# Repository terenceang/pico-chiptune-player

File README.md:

# Pico Chiptune Player

**Version:** 0.8 (JLC Assembly Prep — corrected GPIO map, 0402/0805 passives, LCSC part numbers)  
**Author:** Terence Ang <terenceang@mac.com>  
**Company:** MotionFxDesign  
**License:** [CC BY-NC-SA 4.0](LICENSE) (Creative Commons Attribution-NonCommercial-ShareAlike 4.0 International) — **NOT FOR COMMERCIAL USE**  

---

## Overview

The **Pico Chiptune Player** is an open-hardware music player powered by an on-board **Raspberry Pi RP2354A** microcontroller (QFN-60 with 2 MB internal stacked QSPI NOR flash) driving two authentic **Yamaha YM2149F** Programmable Sound Generators (PSGs), register-compatible with the General Instrument AY-3-8910. Each PSG provides 3 voices, giving **6 independent voices** total, routed through a **software-controlled 4-mode analog stereo/mono mixing matrix** (`2× 74HCT4053D`).

It enables standalone playback of classic AY-3-8910 / YM2149 chiptune music formats (e.g., `.ym`, `.vgm`, `.psg`, `.pt3`, `.sndh`) loaded directly from an onboard microSD card, with song and playback metadata displayed on an I2C OLED display.

---

## Hardware Highlights (Rev 0.8)

- **Microcontroller (`U5`):** Bare **Raspberry Pi RP2354A** (QFN-60, 7×7 mm, 0.4 mm pitch) with **2 MB internal stacked QSPI NOR flash** and all **30 Bank-0 GPIOs (`GPIO0..GPIO29`)** exposed, clocked by a 12 MHz SMD-3225 crystal (`Y1`, `C20`/`C21` = 15 pF, `R16` = 1 kΩ) with internal 1.1 V core buck regulator (`L1` = 3.3 µH) and onboard `BOOTSEL` (`SW4`) and `RESET` (`SW5`) SMD tactile buttons (`TS-1187A`, LCSC `C318884`).
- **USB-C 5V/3A Power & 3-Stage Sequencing (`J1`, `D1`, `U6`, `Q1`, `Q2`):**
  - 16-pin USB 2.0 Type-C receptacle (`J1`) with independent 5.1 kΩ 1% pull-downs (`R21`, `R22`) on `CC1`/`CC2` advertising a fixed 5V/3A sink, plus `USBLC6-2SC6` (`D1`) ESD protection and 27 Ω (`R17`, `R18`) USB series termination.
  - **Stage 1 (`VBUS` → `+3.3V` & `+1V1`):** `AMS1117-3.3` (`U6`) powers `+3.3V` (`RP2354A` `IOVDD`, microSD `J2`, OLED `U2`) and the `RP2354A` internal `+1V1` core regulator immediately on USB plug-in so `RP2354A` I/O pins initialize cleanly with `~RESET` held LOW (`R3` = 10 kΩ).
  - **Stage 2 (`+3.3V` RC-delayed → `+5V`):** RC delay (`R23` = 47 kΩ, `C31` = 100 nF) turns on N-MOSFET `Q2` (`2N7002`), pulling down the gate of high-side P-MOSFET `Q1` (`AO3401A`, with `R28` = 100 kΩ pull-up and `C32` = 10 nF soft-start cap) to switch `VBUS` onto the `+5V` rail **only after `+3.3V` is stable**, preventing unpowered latch-up or back-bias on the 5 V `YM2149F` PSGs (`U1`, `U4`), `74HCT4053D` analog switches (`U8`, `U9`), and `PAM8403` amplifier (`U3`).
  - **Stage 3 (`SD_Amp` on `GPIO21` → `U3` `PAM8403`):** `R13` (10 kΩ pull-down) keeps `PAM8403` `~MUTE` and `~SHDN` LOW during Stage 1 & Stage 2 power-up until firmware drives `GPIO21` HIGH after AC coupling capacitors `C3`/`C10` settle, eliminating power-on pop.
- **Sound Generators (`U1`, `U4`):** 2× Yamaha YM2149F (40-pin DIP, socketed), 6 voices total; a matched pair of AY-3-8910s also fits with `JP1` open.
- **4-Mode Hardware Stereo/Mono Analog Mixing Matrix (`U8`, `U9`):**
  - Dual `74HCT4053D` triple 2:1 analog multiplexers powered from `+5V` (`VCC = +5V`, `VEE = VSS = INH = GND`, 3.3 V TTL-compatible control inputs) controlled by `GPIO14` (`MUX_PAN`), `GPIO15` (`MUX_B_CEN`), `GPIO16` (`MUX_C_CEN`), and `GPIO17` (`MUX_MONO`) with 470 Ω (`R14`, `R15`) `-3 dB` center-channel compensation resistors.
  - Supports **Dual-PSG Split Stereo** (`U1`=Left, `U4`=Right), **ABC Stereo** (`A`=Left, `B`=Center, `C`=Right across both PSGs), **ACB Stereo** (`A`=Left, `C`=Center, `B`=Right across both PSGs), and **True Mono** (`A+B+C` of both PSGs summed equally to Left & Right).
- **Audio Amplifier & Output (`U3`, `J3`, `J4`):**
  - Two passive summing/filtering networks (`R4`,`R5`,`R7`,`R8`,`C4`,`C3` for Left; `R9`,`R10`,`R11`,`R12`,`C9`,`C10` for Right) feeding an on-board **PAM8403 3W+3W filterless Class-D stereo amplifier** (`U3`, SOIC-16).
  - JST-PH 2-pin speaker connectors `J3` (left) / `J4` (right) with bridge-tied outputs for 4–8 Ω speakers.
- **Storage (`J2`):** 4-bit SDIO microSD card socket (Hirose `DM3AT-SF-PEJM5`, LCSC `C114218`) driven by the RP2350 PIO-based `pico_sd_card` driver; card presence detected in software (`R1` 10 kΩ pull-up on `DAT3`).
- **Display (`U2`) & Controls (`SW1..SW5`):** 0.96" SSD1306 128×64 I2C OLED display (`U2`), 3 navigation pushbuttons (`SW1` Play/Pause, `SW2` Next, `SW3` Prev), plus `SW4` (`BOOTSEL`) and `SW5` (`RESET`) — all `TS-1187A` SMD tactiles (LCSC `C318884`).
- **Clock Divider Select (`JP1`):** Solder jumper for the YM2149F ÷2 internal clock divider (`/SEL`, pin 26), shared by both PSGs.

---

## Pinout Summary (`U5` — RP2354A QFN-60)

| GPIO | QFN-60 Pin | Net / Signal | Connected Subsystem |
| :--- | :---: | :--- | :--- |
| **`GPIO0..GPIO3`** | Pins 2..5 | `DA0..DA3` | YM2149F 8-Bit Data Bus Bits 0..3, shared by `U1`/`U4` (Pins 37..34) |
| **`GPIO4..GPIO7`** | Pins 7..10 | `DA4..DA7` | YM2149F 8-Bit Data Bus Bits 4..7, shared by `U1`/`U4` (Pins 33..30) |
| **`GPIO8`** | Pin 12 | `BC1` | PSG1 (`U1`) Bus Control 1 (Pin 29) |
| **`GPIO9`** | Pin 13 | `MCU_CLK` | YM2149F Master Clock Input, shared by `U1`/`U4` (Pin 22 via 33 Ω series `R2`) |
| **`GPIO10`** | Pin 14 | `BDIR` | PSG1 (`U1`) Bus Direction Control (Pin 27) |
| **`GPIO11`** | Pin 15 | `~RESET` | YM2149F Active-Low Reset, shared by `U1`/`U4` (Pin 23) + 10 kΩ `R3` pull-down |
| **`GPIO12`** | Pin 16 | `BC1_2` | PSG2 (`U4`) Bus Control 1 (Pin 29) |
| **`GPIO13`** | Pin 17 | `BDIR2` | PSG2 (`U4`) Bus Direction Control (Pin 27) |
| **`GPIO14`** | Pin 18 | `MUX_PAN` | Stereo Matrix Right/Left Voice Pan (`U9` Pins 9, 10, 11 + 10 kΩ `R24` pull-down) |
| **`GPIO15`** | Pin 19 | `MUX_B_CEN` | Stereo Matrix Voice B Center Enable (`U8` Pin 11 + 10 kΩ `R25` pull-down) |
| **`GPIO16`** | Pin 27 | `MUX_C_CEN` | Stereo Matrix Voice C Center Enable (`U8` Pin 10 + 10 kΩ `R26` pull-down) |
| **`GPIO17`** | Pin 28 | `MUX_MONO` | Stereo Matrix True Mono Bridge Enable (`U8` Pin 9 + 10 kΩ `R27` pull-down) |
| **`GPIO18`** | Pin 29 | `SW_NEXT` | Next Track Button (`SW2`) |
| **`GPIO19`** | Pin 31 | `SW_PLAY` | Play / Pause Button (`SW1`) |
| **`GPIO20`** | Pin 32 | `SW_PREV` | Previous Track Button (`SW3`) |
| **`GPIO21`** | Pin 33 | `SD_Amp` | PAM8403 Audio Amp Enable / Mute (`U3` Pins 5 `~MUTE` & 12 `~SHDN`, `R13` pull-down) |
| **`GPIO22`** | Pin 34 | `SD_DAT0` | MicroSD SDIO Data 0 (`J2` Pin 7) |
| **`GPIO23`** | Pin 35 | `SD_DAT1` | MicroSD SDIO Data 1 (`J2` Pin 8) |
| **`GPIO24`** | Pin 36 | `SD_DAT2` | MicroSD SDIO Data 2 (`J2` Pin 1) |
| **`GPIO25`** | Pin 37 | `SD_DAT3` | MicroSD SDIO Data 3 (`J2` Pin 2 + 10 kΩ `R1` pull-up) |
| **`GPIO26`** | Pin 40 | `SD_CLK` | MicroSD SDIO Clock (`J2` Pin 5) |
| **`GPIO27`** | Pin 41 | `SD_CMD` | MicroSD SDIO Command (`J2` Pin 3) |
| **`GPIO28`** | Pin 42 | `OLED_SDA` | 0.96" OLED I2C0 SDA (`U2` Pin 4) |
| **`GPIO29`** | Pin 43 | `OLED_SCL` | 0.96" OLED I2C0 SCL (`U2` Pin 3) |

---

## 4-Mode Stereo / Mono Mixing Matrix Truth Table

| Mode | `MUX_MONO` (`GPIO17`) | `MUX_B_CEN` (`GPIO15`) | `MUX_C_CEN` (`GPIO16`) | `MUX_PAN` (`GPIO14`) | Left Channel (`AMP_INL`) | Right Channel (`AMP_INR`) | Use Case |
| :--- | :---: | :---: | :---: | :---: | :--- | :--- | :--- |
| **0: Dual-PSG Split (Default)** | `0` | `0` | `0` | `0` | `U1` (`A1 + B1 + C1`) | `U4` (`A2 + B2 + C2`) | 6-voice TurboSound / Dual-PSG tracks (chip 1 Left, chip 2 Right); default at boot via `R24..R27` pull-downs |
| **1: ABC Stereo** | `0` | `1` | `0` | `1` | `A1 + A2` + `0.71×(B1 + B2)` | `C1 + C2` + `0.71×(B1 + B2)` | Standard Western / Atari ST / ZX Spectrum ABC stereo (`A`=Left, `B`=Center `-3 dB`, `C`=Right) |
| **2: ACB Stereo** | `0` | `0` | `1` | `0` | `A1 + A2` + `0.71×(C1 + C2)` | `B1 + B2` + `0.71×(C1 + C2)` | Eastern European / Pentagon / PT3 ACB stereo (`A`=Left, `C`=Center `-3 dB`, `B`=Right) |
| **3: True Mono** | `1` | `0` | `0` | `0` | `0.5×(U1 + U4)` (`A+B+C`) | `0.5×(U1 + U4)` (`A+B+C`) | Classic single-PSG mono chiptunes played identically through both speakers |

**Rev 0.8** is prepared for JLC PCB assembly: every part carries an `LCSC Part #` in the schematic, passives are JLC basic 0402/0805 parts, and the microSD socket (`C114218`) and buttons (`C318884`) are SMD.

For the complete hardware design details, circuit topology, and full Bill of Materials with LCSC part numbers, refer to [HARDWARE.md](HARDWARE.md).

---

## License & Commercial Use Notice

Copyright (c) 2026 Terence Ang <terenceang@mac.com> / MotionFxDesign.

This project is licensed under the **Creative Commons Attribution-NonCommercial-ShareAlike 4.0 International License (CC BY-NC-SA 4.0)**.

> **NOT FOR COMMERCIAL USE**  
> This design, including schematics, PCB layouts, Gerber files, firmware, and documentation, is free for personal, hobby, educational, and non-commercial use.  
> **Commercial manufacture, distribution, sale, or bundling for profit is strictly prohibited** without prior written authorization from Terence Ang (<terenceang@mac.com>).

See the [LICENSE](LICENSE) file for the complete license terms.

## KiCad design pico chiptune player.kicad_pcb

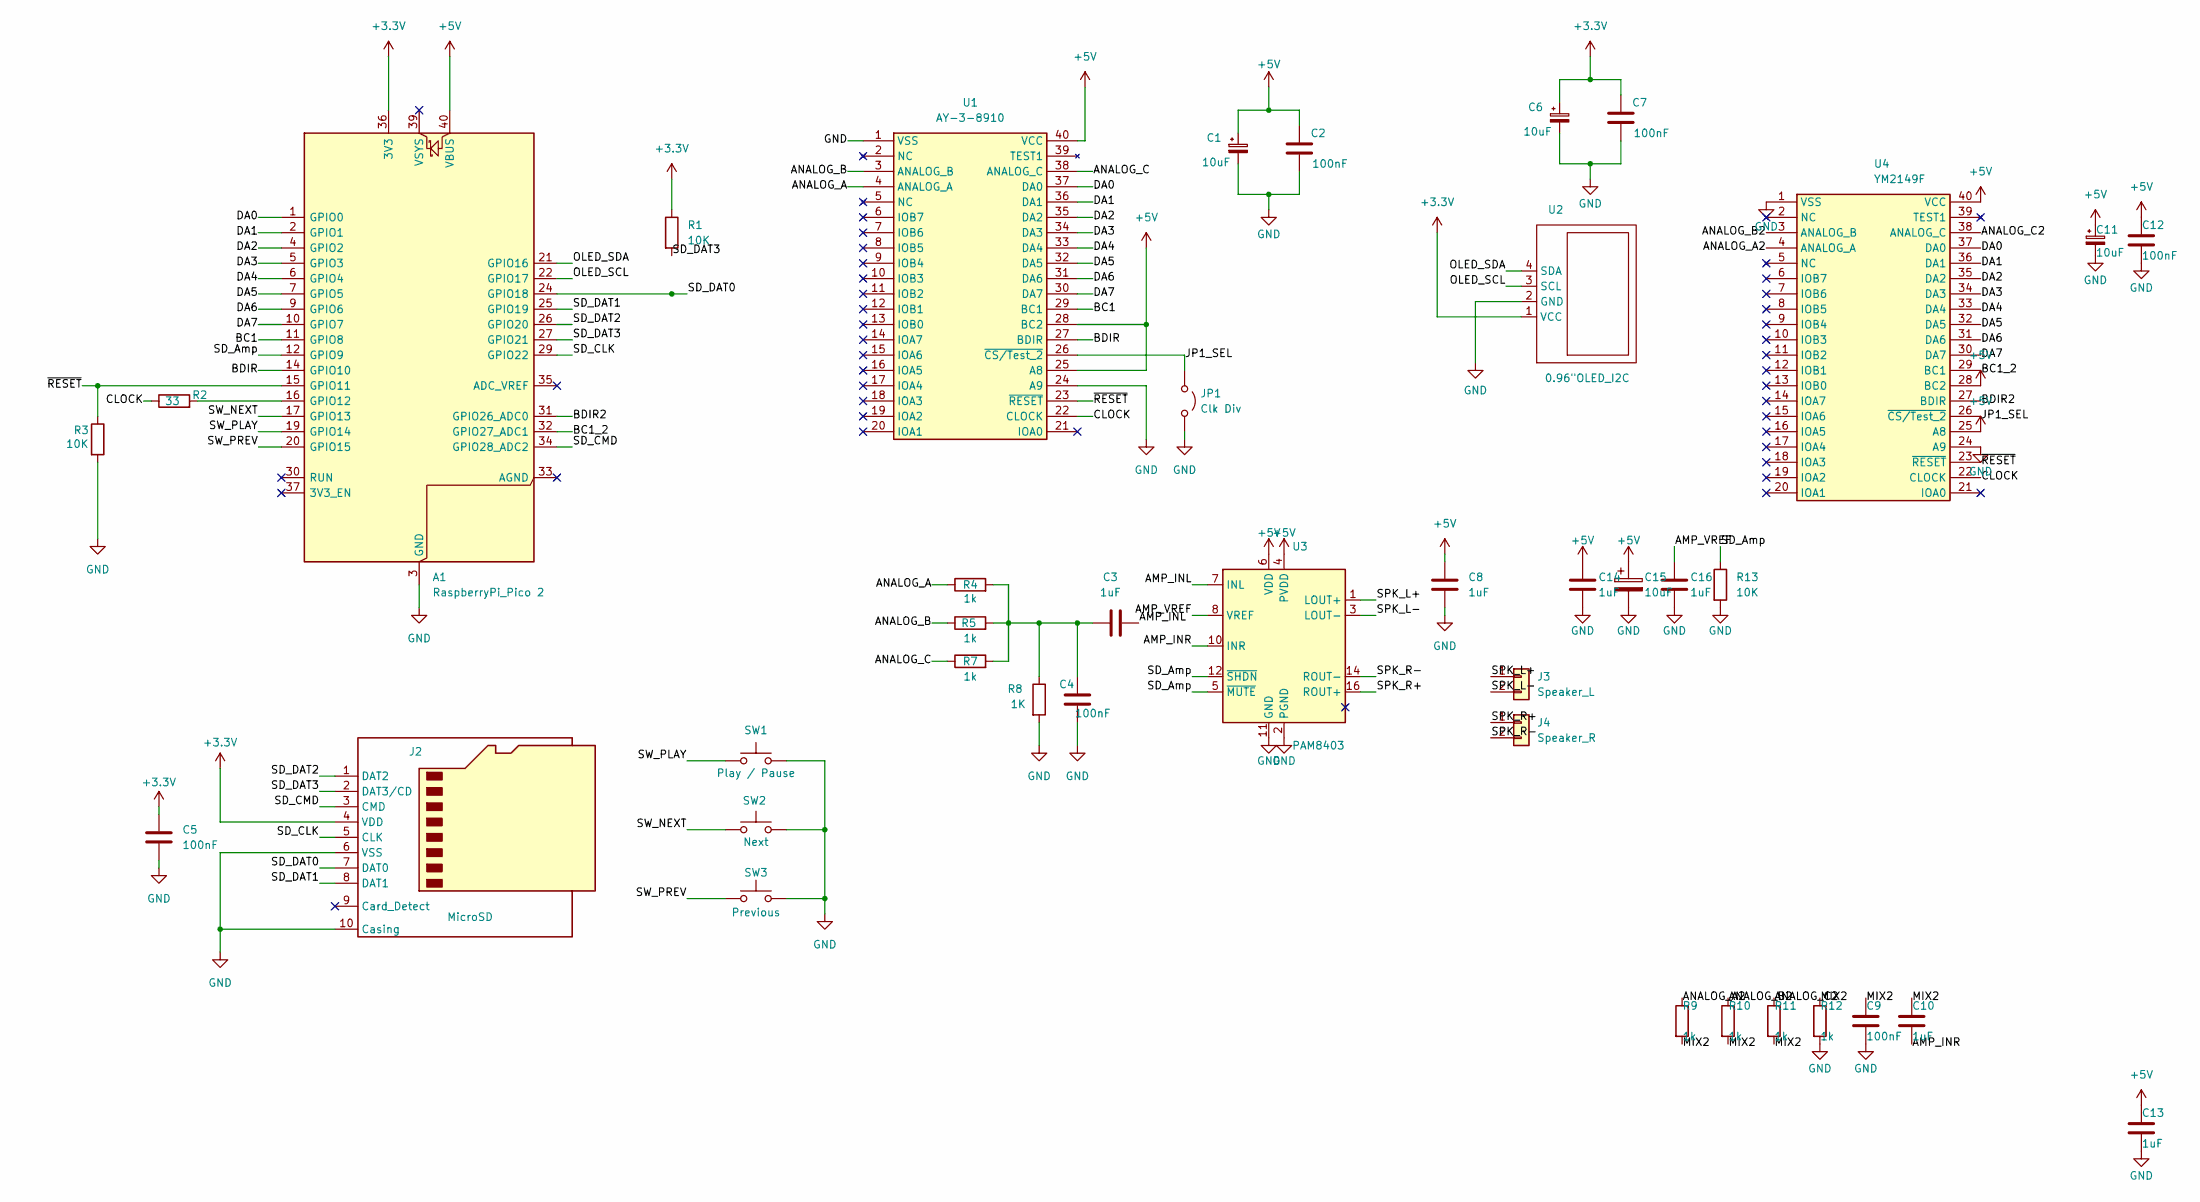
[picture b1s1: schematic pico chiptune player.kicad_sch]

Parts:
A1: RaspberryPi_Pico 2; RPi_Pico_SMD_TH
C1, C6, C15: 10uF; CP_Elec_4x5.4; LCSC Part # C3343
C2, C7: 100nF; C_0805_2012Metric_Pad1.18x1.45mm_HandSolder; LCSC Part # C1711
C3, C8, C10, C13, C14, C16: 1uF; C_0805_2012Metric_Pad1.18x1.45mm_HandSolder; LCSC Part # C28323
C4, C5: 100nF; C_0805_2012Metric_Pad1.18x1.45mm_HandSolder; LCSC Part # C1710
C9, C12: 100nF; C_0805_2012Metric_Pad1.18x1.45mm_HandSolder
C11: 10uF; CP_Elec_4x5.4
J2: MicroSD; LCSC Part # C479742
J3: Speaker_L; JST_PH_B2B-PH-K_1x02_P2.00mm_Vertical; LCSC Part # C131337
J4: Speaker_R; JST_PH_B2B-PH-K_1x02_P2.00mm_Vertical; LCSC Part # C131337
JP1: Clk Div; SolderJumper-2_P1.3mm_Open_TrianglePad1.0x1.5mm
R1, R3, R13: 10K; R_0805_2012Metric_Pad1.20x1.40mm_HandSolder; LCSC Part # C17414
R2: 33; R_0805_2012Metric_Pad1.20x1.40mm_HandSolder; LCSC Part # C17634
R4, R5, R7: 1k; R_0805_2012Metric_Pad1.20x1.40mm_HandSolder; LCSC Part # C17513
R8: 1K; R_0805_2012Metric_Pad1.20x1.40mm_HandSolder; LCSC Part # C17513
R9, R10, R11, R12: 1k; R_0805_2012Metric_Pad1.20x1.40mm_HandSolder
SW1: Play / Pause; SW_PUSH_6mm; LCSC Part # C17513
SW2: Next; SW_PUSH_6mm; LCSC Part # C114217
SW3: Previous; SW_PUSH_6mm; LCSC Part # C12740
U1: AY-3-8910; DIP-40_W15.24mm
U2: 0.96"OLED_I2C; OLED 0.96 I2C
U3: PAM8403; SOIC-16_3.9x9.9mm_P1.27mm; LCSC Part # C5122557
U4: YM2149F; DIP-40_W15.24mm

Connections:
+3.3V: A1.36 (3V3), C5.1, C6.1, C7.1, J2.4 (VDD), R1.1, U2.1 (VCC)
+5V: A1.40 (VBUS), C1.1, C2.1, C8.1, C11.1, C12.1, C13.1, C14.1, C15.1, U1.25 (A8), U1.28 (BC2), U1.40 (VCC), U3.4 (PVDD), U3.6 (VDD), U3.13 (PVDD), U4.25 (A8), U4.28 (BC2), U4.40 (VCC)
/AMP_INL: C3.2, U3.7 (INL)
/AMP_INR: C10.2, U3.10 (INR)
/AMP_VREF: C16.1, U3.8 (VREF)
/ANALOG_A: R4.1, U1.4 (ANALOG_A)
/ANALOG_A2: R9.1, U4.4 (ANALOG_A)
/ANALOG_B: R5.1, U1.3 (ANALOG_B)
/ANALOG_B2: R10.1, U4.3 (ANALOG_B)
/ANALOG_C: R7.1, U1.38 (ANALOG_C)
/ANALOG_C2: R11.1, U4.38 (ANALOG_C)
/BC1: A1.11 (GPIO8), U1.29 (BC1)
/BC1_2: A1.32 (GPIO27_ADC1), U4.29 (BC1)
/BDIR: A1.14 (GPIO10), U1.27 (BDIR)
/BDIR2: A1.31 (GPIO26_ADC0), U4.27 (BDIR)
/CLOCK: R2.1, U1.22 (CLOCK), U4.22 (CLOCK)
/DA0: A1.1 (GPIO0), U1.37 (DA0), U4.37 (DA0)
/DA1: A1.2 (GPIO1), U1.36 (DA1), U4.36 (DA1)
/DA2: A1.4 (GPIO2), U1.35 (DA2), U4.35 (DA2)
/DA3: A1.5 (GPIO3), U1.34 (DA3), U4.34 (DA3)
/DA4: A1.6 (GPIO4), U1.33 (DA4), U4.33 (DA4)
/DA5: A1.7 (GPIO5), U1.32 (DA5), U4.32 (DA5)
/DA6: A1.9 (GPIO6), U1.31 (DA6), U4.31 (DA6)
/DA7: A1.10 (GPIO7), U1.30 (DA7), U4.30 (DA7)
/JP1_SEL: JP1.1 (A), U1.26 (~CS/Test_2), U4.26 (~CS/Test_2)
/MIX2: C9.1, C10.1, R9.2, R10.2, R11.2, R12.1
/OLED_SCL: A1.22 (GPIO17), U2.3 (SCL)
/OLED_SDA: A1.21 (GPIO16), U2.4 (SDA)
/SD_Amp: A1.12 (GPIO9), R13.1, U3.5 (~MUTE), U3.12 (~SHDN)
/SD_CLK: A1.29 (GPIO22), J2.5 (CLK)
/SD_CMD: A1.34 (GPIO28_ADC2), J2.3 (CMD)
/SD_DAT0: A1.24 (GPIO18), J2.7 (DAT0)
/SD_DAT1: A1.25 (GPIO19), J2.8 (DAT1)
/SD_DAT2: A1.26 (GPIO20), J2.1 (DAT2)
/SD_DAT3: A1.27 (GPIO21), J2.2 (DAT3/CD), R1.2
/SPK_L+: J3.1, U3.1 (LOUT+)
/SPK_L-: J3.2, U3.3 (LOUT-)
/SPK_R+: J4.1, U3.16 (ROUT+)
/SPK_R-: J4.2, U3.14 (ROUT-)
/SW_NEXT: A1.17 (GPIO13), SW2.1
/SW_PLAY: A1.19 (GPIO14), SW1.1
/SW_PREV: A1.20 (GPIO15), SW3.1
/~RESET: A1.15 (GPIO11), R3.1, U1.23 (~RESET), U4.23 (~RESET)
GND: A1.3 (GND), A1.8 (GND), A1.13 (GND), A1.18 (GND), A1.23 (GND), A1.28 (GND), A1.38 (GND), C1.2, C2.2, C4.2, C5.2, C6.2, C7.2, C8.2, C9.2, C11.2, C12.2, C13.2, C14.2, C15.2, C16.2, J2.6 (VSS), J2.10 (Casing), JP1.2 (B), R3.2, R8.2, R12.2, R13.2, SW1.2, SW2.2, SW3.2, U1.1 (VSS), U1.24 (A9), U2.2 (GND), U3.2 (PGND), U3.11 (GND), U3.15 (PGND), U4.1 (VSS), U4.24 (A9)
unnamed: A1.16 (GPIO12), R2.2
unnamed: C3.1, C4.1, R4.2, R5.2, R7.2, R8.1

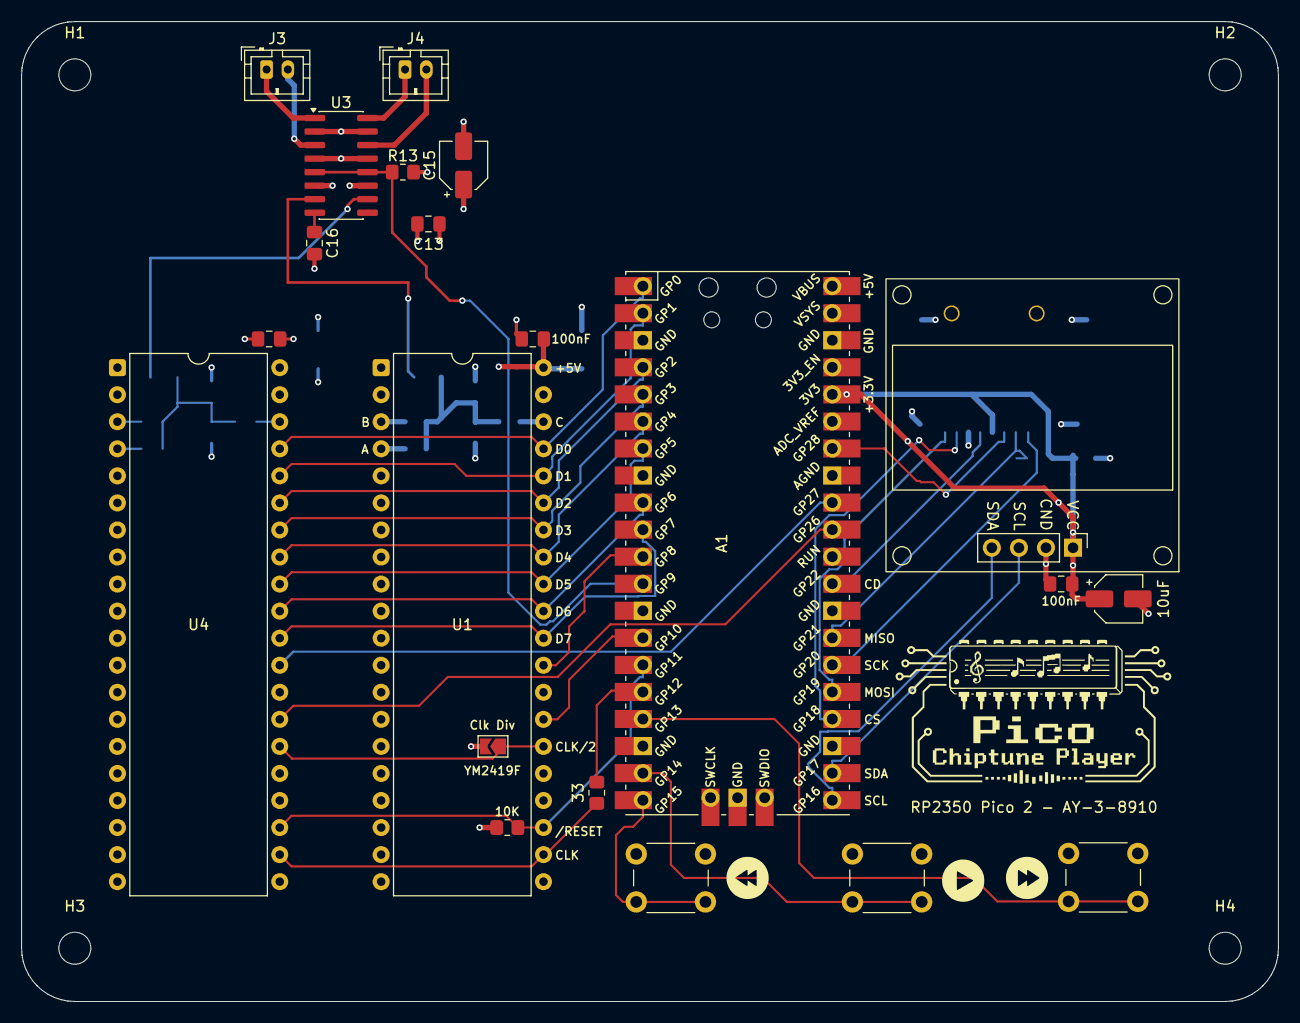
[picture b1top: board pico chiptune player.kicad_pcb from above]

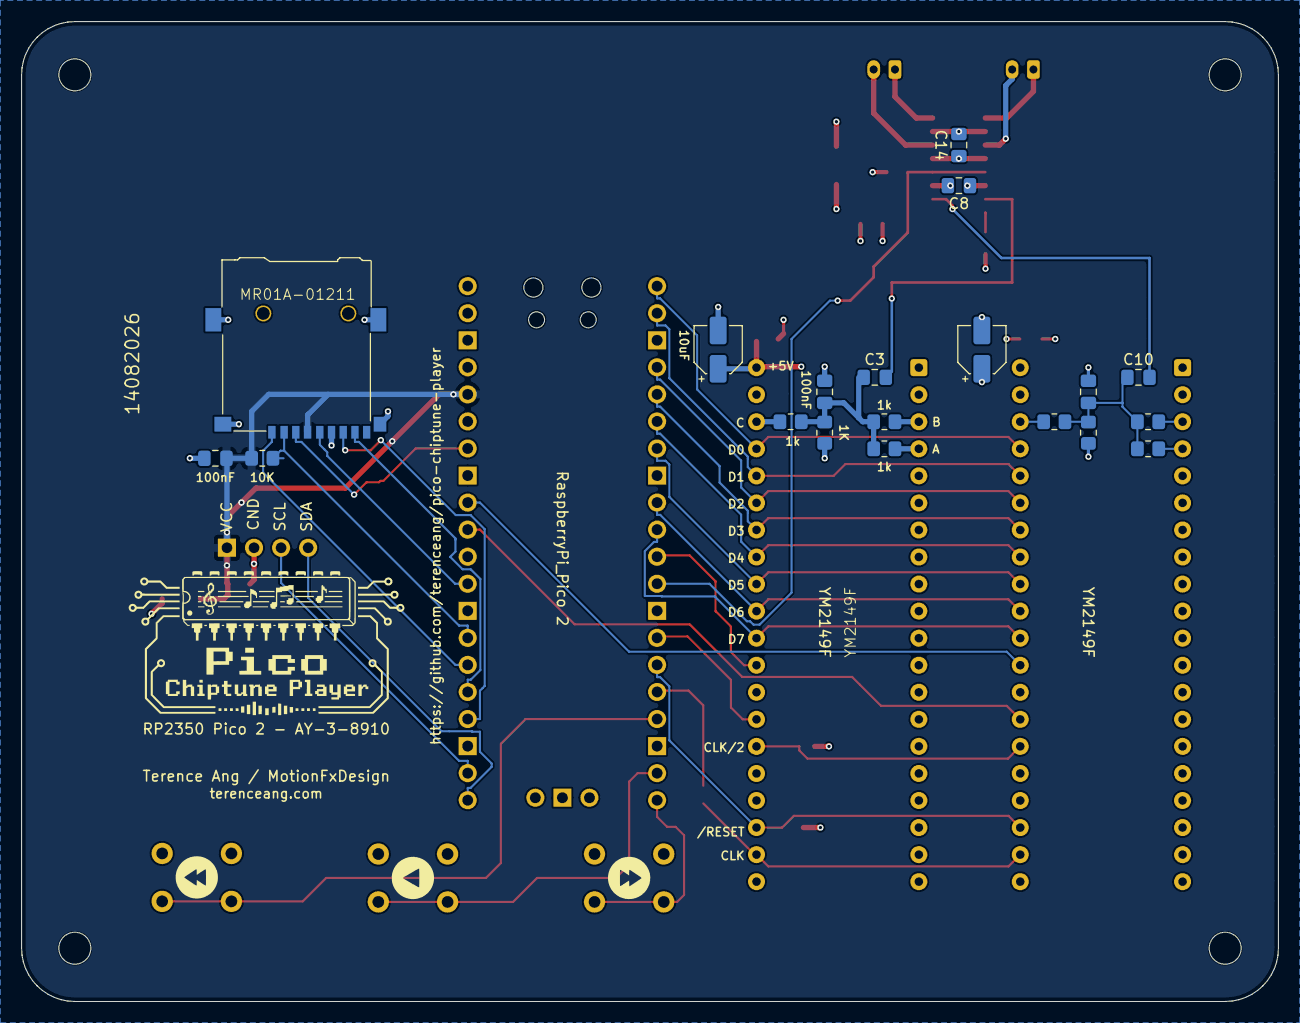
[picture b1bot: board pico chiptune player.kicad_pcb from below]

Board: 4 copper layers, 118.0 x 92.0 mm, 44 parts (19 on the bottom side), 46 nets.

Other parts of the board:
H1, H2, H3, H4: MountingHole_3mm
